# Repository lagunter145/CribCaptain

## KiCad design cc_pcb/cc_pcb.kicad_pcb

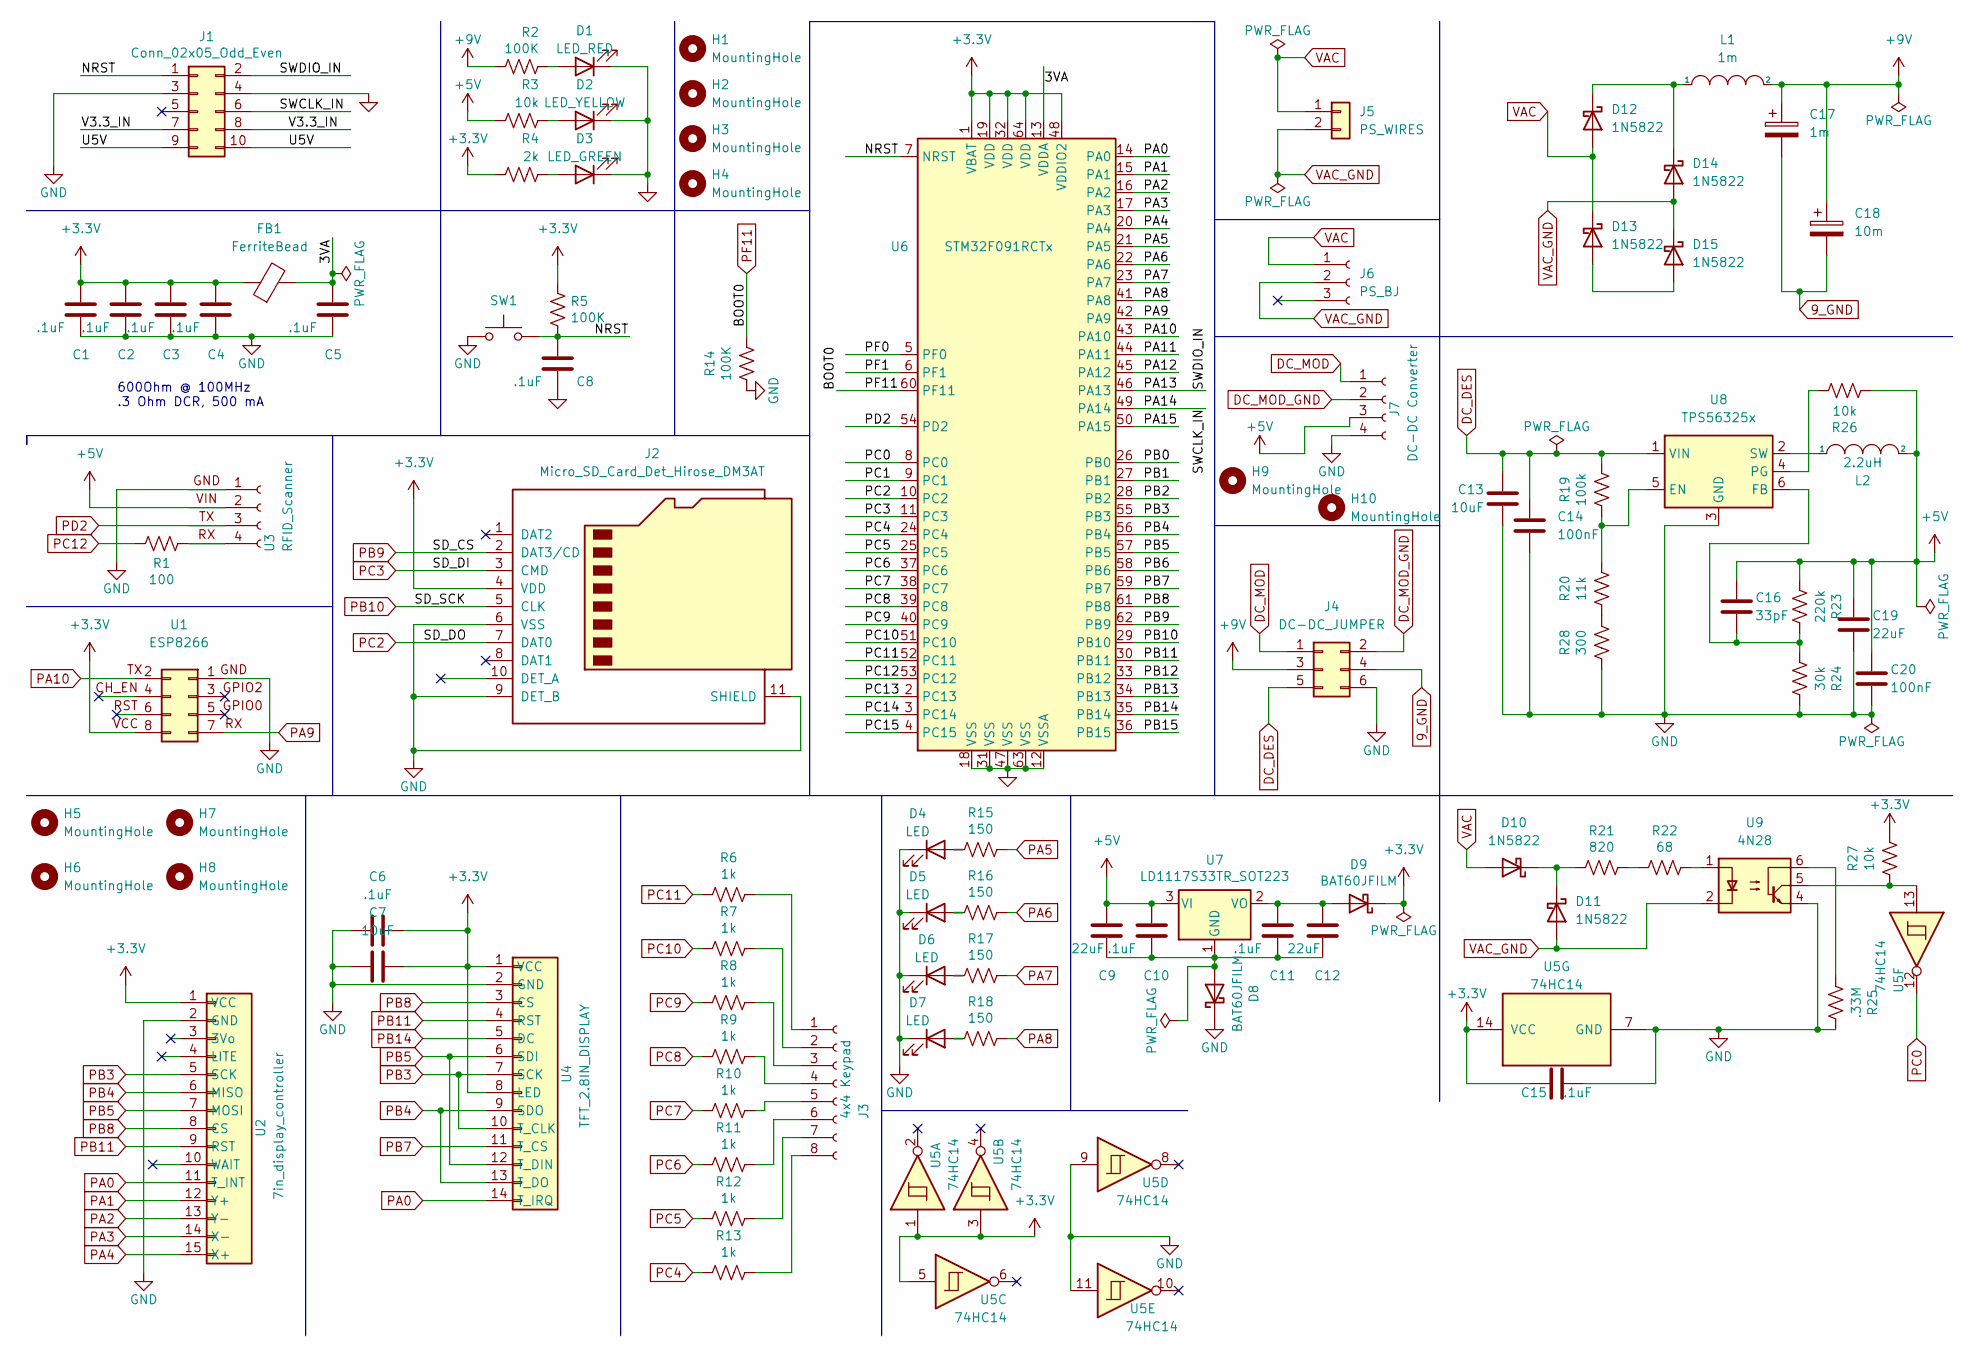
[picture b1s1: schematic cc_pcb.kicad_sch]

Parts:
C1, C2, C3, C4, C5, C6, C8, C10, C11, C15: .1uF; C_0805_2012Metric_Pad1.18x1.45mm_HandSolder
C7, C13: 10uF; C_0805_2012Metric_Pad1.18x1.45mm_HandSolder
C9, C12, C19: 22uF; C_0805_2012Metric_Pad1.18x1.45mm_HandSolder
C14, C20: 100nF; C_0805_2012Metric_Pad1.18x1.45mm_HandSolder
C16: 33pF; C_0805_2012Metric_Pad1.18x1.45mm_HandSolder
C17: 1m; CP_Radial_D12.5mm_P5.00mm
C18: 10m; C_Radial_D18.0mm_H35.5mm_P7.50mm
D1: LED_RED; LED_0805_2012Metric_Pad1.15x1.40mm_HandSolder
D2: LED_YELLOW; LED_0805_2012Metric_Pad1.15x1.40mm_HandSolder
D3: LED_GREEN; LED_0805_2012Metric_Pad1.15x1.40mm_HandSolder
D4, D5, D6, D7: LED; LED_D3.0mm
D8, D9: BAT60JFILM; D_SOD-323
D10, D11, D12, D13, D14, D15: 1N5822; DIO_1N5822
FB1: FerriteBead; R_0805_2012Metric_Pad1.20x1.40mm_HandSolder
H1, H2, H3, H4: MountingHole; MountingHole_8.4mm_M8
H5, H6, H7, H8, H9, H10: MountingHole; MountingHole_2.2mm_M2_ISO7380
J1: Conn_02x05_Odd_Even; IDC-Header_2x05_P2.54mm_Vertical
J2: Micro_SD_Card_Det_Hirose_DM3AT; microSD_HC_Hirose_DM3AT-SF-PEJM5
J3: 4x4 Keypad; 4x4_keypad
J4: DC-DC_JUMPER; PinSocket_2x03_P1.27mm_Vertical
J5: PS_WIRES; PS_2_Wire
J6: PS_BJ; barrel_jack_adapter
J7: DC-DC Converter; 7.5Vdc-5Vdc_buck_converter
L1: 1m; L_Toroid_Vertical_L54.0mm_W23.8mm_P20.10mm_Bourns_5700
L2: 2.2uH; L_0805_2012Metric_Pad1.15x1.40mm_HandSolder
R1: 100; R_0805_2012Metric_Pad1.20x1.40mm_HandSolder
R2, R5, R14: 100K; R_0805_2012Metric_Pad1.20x1.40mm_HandSolder
R3, R26, R27: 10k; R_0805_2012Metric_Pad1.20x1.40mm_HandSolder
R4: 2k; R_0805_2012Metric_Pad1.20x1.40mm_HandSolder
R6, R7, R8, R9, R10, R11, R12, R13: 1k; R_0805_2012Metric_Pad1.20x1.40mm_HandSolder
R15, R16, R17, R18: 150; R_0805_2012Metric_Pad1.20x1.40mm_HandSolder
R19: 100k; R_0805_2012Metric_Pad1.20x1.40mm_HandSolder
R20: 11k; R_0805_2012Metric_Pad1.20x1.40mm_HandSolder
R21: 820; R_0805_2012Metric_Pad1.20x1.40mm_HandSolder
R22: 68; R_0805_2012Metric_Pad1.20x1.40mm_HandSolder
R23: 220k; R_0805_2012Metric_Pad1.20x1.40mm_HandSolder
R24: 30k; R_0805_2012Metric_Pad1.20x1.40mm_HandSolder
R25: .33M; R_0805_2012Metric_Pad1.20x1.40mm_HandSolder
R28: 300; R_0805_2012Metric_Pad1.20x1.40mm_HandSolder
SW1: SW_Push; SW_SPST_PTS645
U1: ESP8266; XCVR_ESP8266-01_ESP-01
U2: 7in_display_controller; RA8875_TFT_Breakout
U3: RFID_Scanner; RFID_Reader_PCB
U4: TFT_2.8IN_DISPLAY; tft_2.8in_touch_display
U5: 74HC14; SN74HC14N
U6: STM32F091RCTx; LQFP-64_10x10mm_P0.5mm
U7: LD1117S33TR_SOT223; 5-3.3_buck_converter
U8: TPS56325x; SOT-563
U9: 4N28; DIP-6_W7.62mm

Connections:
9_GND: C17.2, C18.2, J4.4
+3V3: C1.1, C2.1, C3.1, C4.1, C6.2, C7.2, C15.1, D9.1 (K), FB1.1, J2.4 (VDD), R4.1, R5.1, R27.1, U1.8, U2.1 (VCC), U4.1 (VCC), U4.8 (LED), U5.1, U5.3, U5.5, U5.14 (VCC), U6.1 (VBAT), U6.19 (VDD), U6.32 (VDD), U6.48 (VDDIO2), U6.64 (VDD)
+5V: C9.1, C10.1, C16.1, C19.1, C20.1, J7.3, L2.2, R3.1, R23.2, R26.2, U3.2, U7.3 (VI)
+9V: C17.1, C18.1, J4.3, L1.2, R2.1
/3VA: C5.1, FB1.2, U6.13 (VDDA)
/NRST: C8.1, J1.1, R5.2, SW1.2, U6.7 (NRST)
/PA11: U6.44 (PA11)
/PA12: U6.45 (PA12)
/PA13: J1.2, U6.46 (PA13)
/PA14: J1.6, U6.49 (PA14)
/PA15: U6.50 (PA15)
/PB0: U6.26 (PB0)
/PB1: U6.27 (PB1)
/PB2: U6.28 (PB2)
/PB6: U6.58 (PB6)
/PB12: U6.33 (PB12)
/PB13: U6.34 (PB13)
/PB15: U6.36 (PB15)
/PC1: U6.9 (PC1)
/PC13: U6.2 (PC13)
/PC14: U6.3 (PC14)
/PC15: U6.4 (PC15)
/PF0: U6.5 (PF0)
/PF1: U6.6 (PF1)
/U5V: J1.9, J1.10
/V3.3_IN: J1.7, J1.8
DC_DES: C13.1, C14.1, J4.5, R19.1, U8.1 (VIN)
DC_MOD: J4.1, J7.1
DC_MOD_GND: J4.2, J7.2
GND: C1.2, C2.2, C3.2, C4.2, C5.2, C6.1, C7.1, C8.2, C13.2, C14.2, C15.2, C19.2, C20.2, D1.1 (K), D2.1 (K), D3.1 (K), D4.1 (K), D5.1 (K), D6.1 (K), D7.1 (K), D8.1 (K), J1.3, J1.4, J2.6 (VSS), J2.9 (DET_B), J2.11 (SHIELD), J4.6, J7.4, R14.2, R24.1, R25.1, R28.2, SW1.1, U1.1, U2.2 (GND), U3.1, U4.2 (GND), U5.7 (GND), U5.9, U5.11, U6.12 (VSSA), U6.18 (VSS), U6.31 (VSS), U6.47 (VSS), U6.63 (VSS), U8.3 (GND), U9.4
unnamed: C9.2, C10.2, C11.2, C12.2, D8.2 (A), U7.1 (GND)
unnamed: C11.1, C12.1, D9.2 (A), U7.2 (VO)
unnamed: C16.2, R23.1, R24.2, U8.6 (FB)
unnamed: D1.2 (A), R2.2
unnamed: D2.2 (A), R3.2
unnamed: D3.2 (A), R4.2
unnamed: D4.2 (A), R15.2
unnamed: D5.2 (A), R16.2
unnamed: D6.2 (A), R17.2
unnamed: D7.2 (A), R18.2
unnamed: D10.1 (K), D11.1 (K), R21.2
unnamed: D12.1 (K), D14.1 (K), L1.1
unnamed: D13.2 (A), D15.2 (A)
unnamed: J3.1, R6.1
unnamed: J3.2, R7.1
unnamed: J3.3, R8.1
unnamed: J3.4, R9.1
unnamed: J3.5, R10.1
unnamed: J3.6, R11.1
unnamed: J3.7, R12.1
unnamed: J3.8, R13.1
unnamed: L2.1, U8.2 (SW)
unnamed: R1.1, U3.4
unnamed: R19.2, R20.1, U8.5 (EN)
unnamed: R20.2, R28.1
unnamed: R21.1, R22.2
unnamed: R22.1, U9.1
unnamed: R25.2, U9.6
unnamed: R26.1, U8.4 (PG)
unnamed: R27.2, U5.13, U9.5
PA0: U2.11 (T_INT), U4.14 (T_IRQ), U6.14 (PA0)
PA1: U2.12 (Y+), U6.15 (PA1)
PA2: U2.13 (Y-), U6.16 (PA2)
PA3: U2.14 (X-), U6.17 (PA3)
PA4: U2.15 (X+), U6.20 (PA4)
PA5: R15.1, U6.21 (PA5)
PA6: R16.1, U6.22 (PA6)
PA7: R17.1, U6.23 (PA7)
PA8: R18.1, U6.41 (PA8)
PA9: U1.7, U6.42 (PA9)
PA10: U1.2, U6.43 (PA10)
PB3: U2.5 (SCK), U4.7 (SCK), U4.10 (T_CLK), U6.55 (PB3)
PB4: U2.6 (MISO), U4.9 (SDO), U4.13 (T_DO), U6.56 (PB4)
PB5: U2.7 (MOSI), U4.6 (SDI), U4.12 (T_DIN), U6.57 (PB5)
PB7: U4.11 (T_CS), U6.59 (PB7)
PB8: U2.8 (CS), U4.3 (CS), U6.61 (PB8)
PB9: J2.2 (DAT3/CD), U6.62 (PB9)
PB10: J2.5 (CLK), U6.29 (PB10)
PB11: U2.9 (RST), U4.4 (RST), U6.30 (PB11)
PB14: U4.5 (DC), U6.35 (PB14)
PC0: U5.12, U6.8 (PC0)
PC2: J2.7 (DAT0), U6.10 (PC2)
PC3: J2.3 (CMD), U6.11 (PC3)
PC4: R13.2, U6.24 (PC4)
PC5: R12.2, U6.25 (PC5)
PC6: R11.2, U6.37 (PC6)
PC7: R10.2, U6.38 (PC7)
PC8: R9.2, U6.39 (PC8)
PC9: R8.2, U6.40 (PC9)
PC10: R7.2, U6.51 (PC10)
PC11: R6.2, U6.52 (PC11)
PC12: R1.2, U6.53 (PC12)
PD2: U3.3, U6.54 (PD2)
PF11: R14.1, U6.60 (PF11)
VAC: D10.2 (A), D12.2 (A), D13.1 (K), J5.1, J6.1
VAC_GND: D11.2 (A), D14.2 (A), D15.1 (K), J5.2, J6.2, U9.2

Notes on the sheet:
600Ohm @ 100MHz .3 Ohm DCR, 500 mA

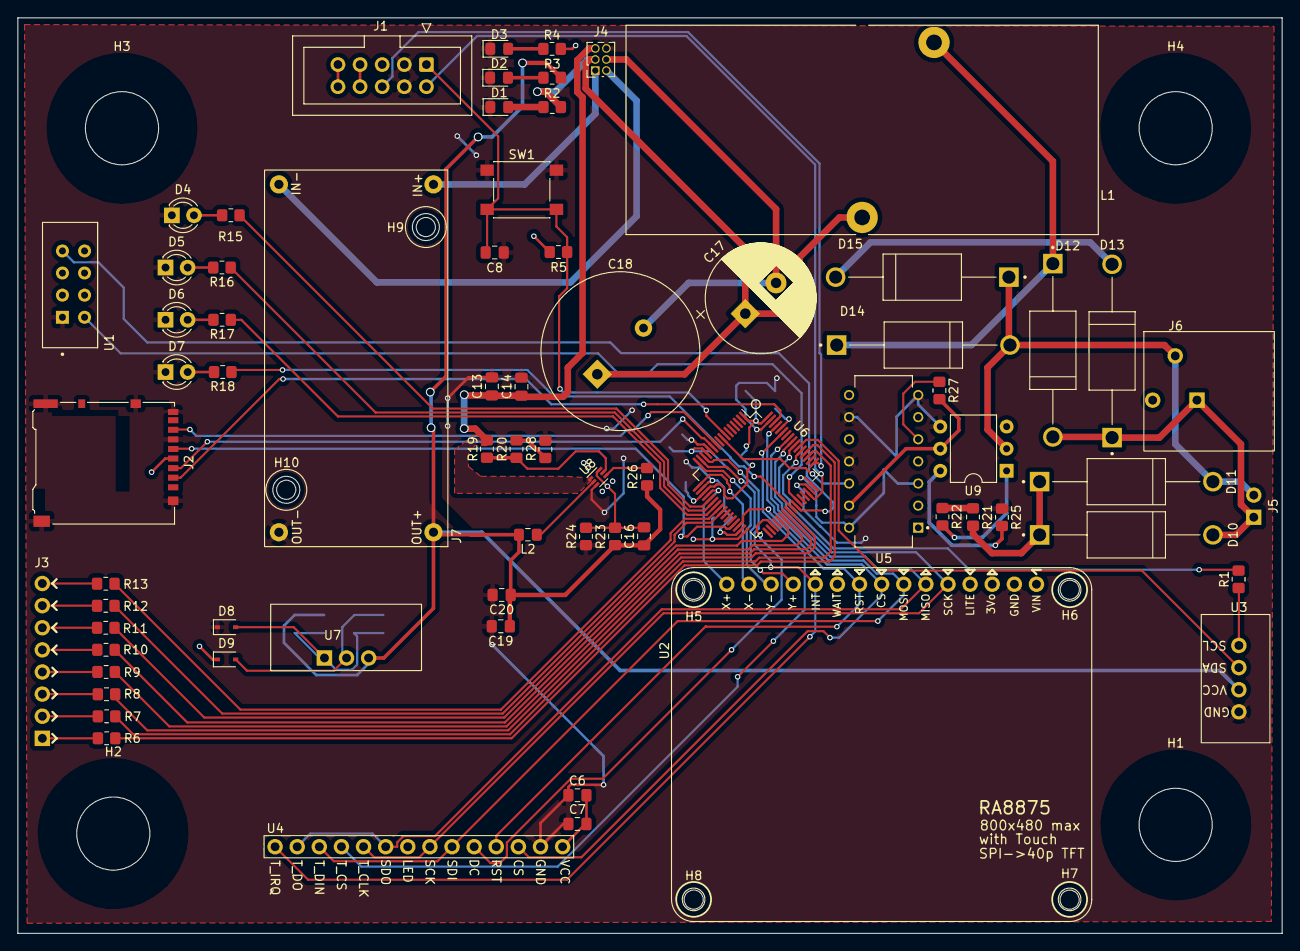
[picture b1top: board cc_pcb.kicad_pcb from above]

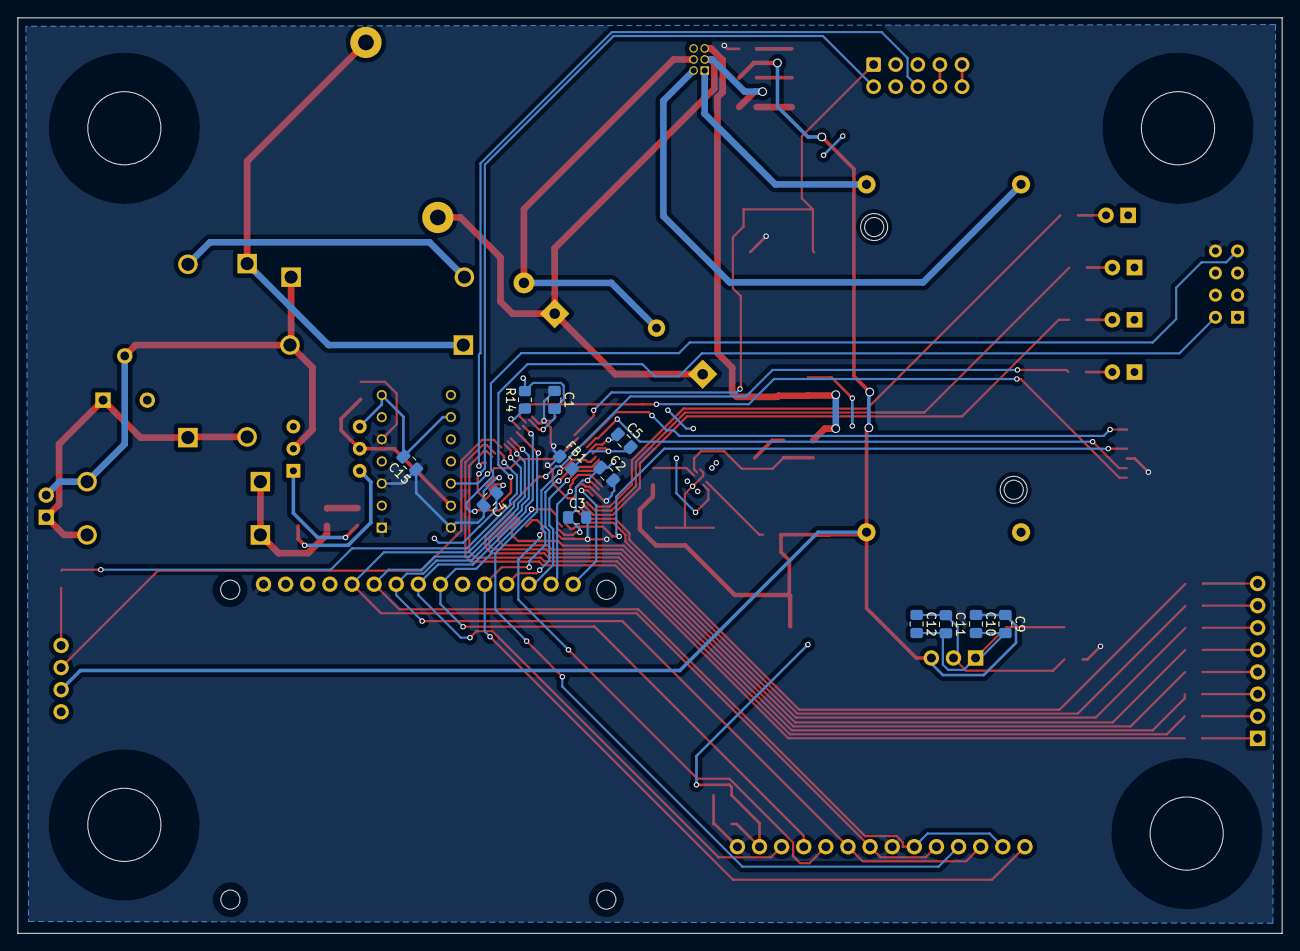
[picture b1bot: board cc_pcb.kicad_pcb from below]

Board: 2 copper layers, 145.2 x 105.1 mm, 93 parts (12 on the bottom side), 80 nets.

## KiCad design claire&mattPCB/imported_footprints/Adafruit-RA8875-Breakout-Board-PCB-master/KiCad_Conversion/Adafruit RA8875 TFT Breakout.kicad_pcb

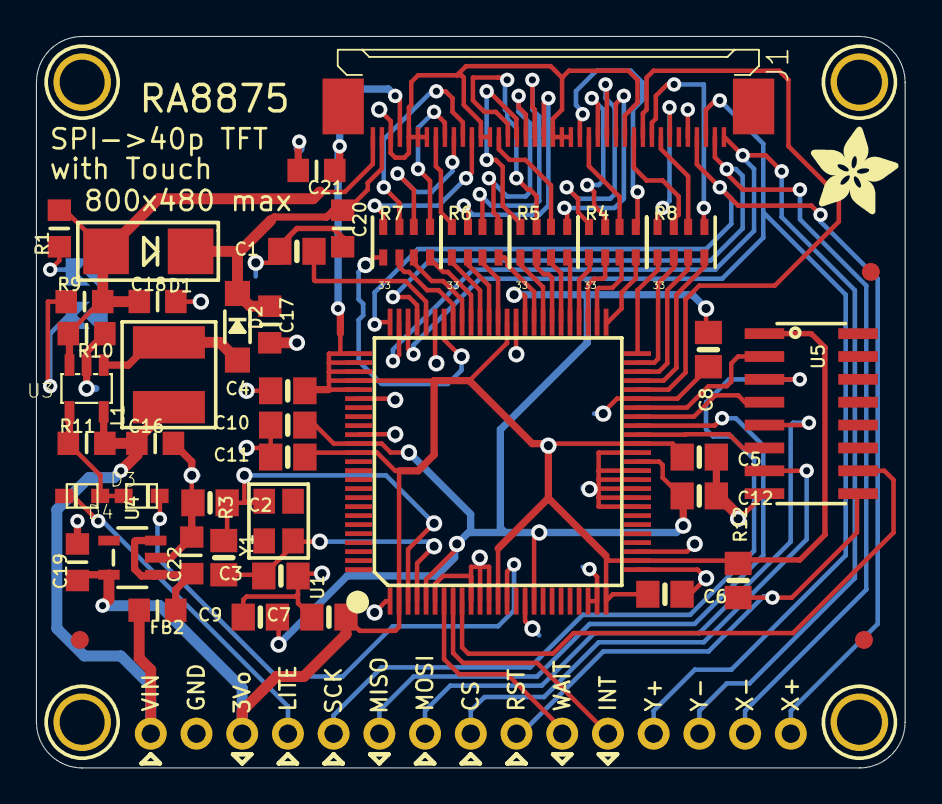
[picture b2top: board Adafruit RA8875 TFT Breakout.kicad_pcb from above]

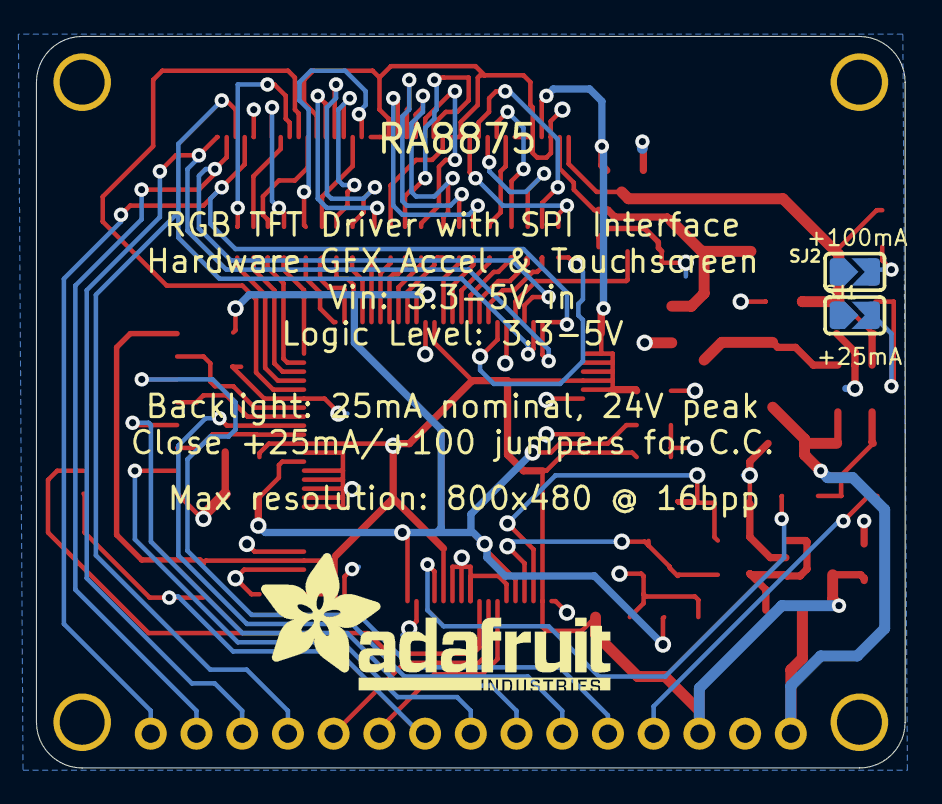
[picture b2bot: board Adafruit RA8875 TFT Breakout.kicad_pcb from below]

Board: 2 copper layers, 48.3 x 40.6 mm, 54 parts (3 on the bottom side), 72 nets.

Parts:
C1, C4, C5, C6, C7, C8, C9, C10, C11, C12: 0.1uF; 0805-NO
C2, C3: 20pF; 0805-NO
C16, C22: 10uF; _0805MP
C17, C20: 1uF; _0805MP
C18: 0.1uF; _0805MP
C19, C21: 10µF; _0805MP
D1: MM3Z24VT1G; SMADIODE
D2: MBR0540; SOD-123
D3, D4: 1N4148; SOD-323F
FB2: Ferrite; _0805MP
FID1, FID2, FID3: FIDUCIAL""; FIDUCIAL_1MM
J1: 40PINFPCM4-1734839-0; 4-1734839-0
JP1: Breakout; 1X15-CB
L1: 6.8uH large inductor; INDUCTOR_5X5MM_NR5040_NOTHERMALS
R1: 3Ω; _0805MP
R3: 1M; 0805-NO
R4, R5, R6, R7, R8: 33; RESPACK_4X0603
R9, R10: 12Ω; _0805MP
R11: 10K; _0805MP
R12: 10K; 0805-NO
SJ1: +25mA; SOLDERJUMPER_ARROW_NOPASTE
SJ2: +100mA; SOLDERJUMPER_ARROW_NOPASTE
U1: RA8875; LQFP100
U3: FAN5333BSX; SOT23-5@1
U4: MIC5225-3.3v; SOT23-5
U5: 74HC4050; SOIC16
U$18: ADAFRUIT_5MM
U$21, U$22, U$23, U$24: MOUNTINGHOLE2.5; MOUNTINGHOLE_2.5_PLATED
U$25: ADAFRUIT_TEXT_20MM
Y1: 20MHz; CRYSTAL_3.2X2.5

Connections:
1.5V: C8.1, C9.1, C10.1, C12.1, U1.5, U1.17, U1.38, U1.60, U1.86
+3V3: C4.1, C5.1, C6.1, C7.1, C11.1, C19.1, C21.1, J1.4, JP1.13, R12.2, U1.2, U1.13, U1.25, U1.27, U1.40, U1.62, U1.76, U1.77, U1.78, U1.79, U1.80, U1.87, U4.5, U5.1
+24V: C17.1, C20.1, D1.C, D2.C, J1.2
B3: J1.24, R4.5
B4: J1.25, R4.6
B5: J1.26, R4.7
B6: J1.27, R4.8
B7: J1.28, R5.5
BACKLITE: D4.C, JP1.12
CS: JP1.8, U5.7
DE: J1.34, R8.8
G2: J1.15, R5.6
G3: J1.16, R5.7
G4: J1.17, R5.8
G5: J1.18, R6.5
G6: J1.19, R6.6
G7: J1.20, R6.7
GND: C1.2, C2.1, C3.1, C4.2, C5.2, C6.2, C7.2, C8.2, C9.2, C10.2, C11.2, C12.2, C16.2, C17.2, C18.2, C19.2, C20.2, C21.2, C22.2, J1.3, J1.5, J1.6, J1.7, J1.13, J1.14, J1.21, J1.22, J1.23, J1.29, J1.36, JP1.14, R10.1, SJ1.1, SJ2.1, U1.1, U1.6, U1.10, U1.11, U1.12, U1.16, U1.23, U1.24, U1.26, U1.28, U1.33, U1.34, U1.35, U1.36, U1.37, U1.39, U1.45, U1.61, U1.70, U1.81, U1.85, U3.2, U4.2, U5.8
HSYNC: J1.32, R8.5
INT: JP1.5, U1.8
LEDK: C18.1, D1.A, J1.1, R1.2, R9.2, R10.2, U3.3
MISO: JP1.10, U1.42
MOSI: JP1.9, U5.5
MOSI_3V: U1.43, U5.4
unnamed: D2.A, L1.P$2, U3.1
unnamed: C2.2, R3.2, U1.3, Y1.2
unnamed: C1.1, U1.71
unnamed: R4.4, U1.51
unnamed: R4.3, U1.52
unnamed: R4.2, U1.53
unnamed: R4.1, U1.54
unnamed: R5.4, U1.55
unnamed: R5.3, U1.56
unnamed: R5.2, U1.57
unnamed: R5.1, U1.58
unnamed: R6.4, U1.59
unnamed: R6.3, U1.63
unnamed: R6.2, U1.64
unnamed: R6.1, U1.65
unnamed: R7.4, U1.66
unnamed: R7.3, U1.67
unnamed: R7.2, U1.68
unnamed: R7.1, U1.69
unnamed: R8.1, U1.50
unnamed: R8.2, U1.49
unnamed: R8.3, U1.48
unnamed: R8.4, U1.47
unnamed: R9.1, SJ1.2
unnamed: C22.1, FB2.1, U4.1, U4.3
unnamed: R1.1, SJ2.2
unnamed: C3.2, R3.1, U1.4, Y1.1
ON/OFF: J1.31, U1.46
PIXCLK: J1.30, R8.7
PWM0: D3.C, U1.14
R3: J1.8, R6.8
R4: J1.9, R7.5
R5: J1.10, R7.6
R6: J1.11, R7.7
R7: J1.12, R7.8
RESET: JP1.7, R12.1, U5.9
RESET_3V: U1.9, U5.10
SCK: JP1.11, U5.3
SHDN: D3.A, D4.A, R11.1, U3.4
SPI_CLK_3V: U1.44, U5.2
SPI_CS_3V: U1.41, U5.6
VIN: C16.1, FB2.2, JP1.15, L1.P$1, R11.2, U3.5
VSYNC: J1.33, R8.6
WAIT: JP1.6, U1.7
X+: J1.37, JP1.1, U1.75
X-: J1.39, JP1.2, U1.72
Y+: J1.38, JP1.4, U1.73
Y-: J1.40, JP1.3, U1.74

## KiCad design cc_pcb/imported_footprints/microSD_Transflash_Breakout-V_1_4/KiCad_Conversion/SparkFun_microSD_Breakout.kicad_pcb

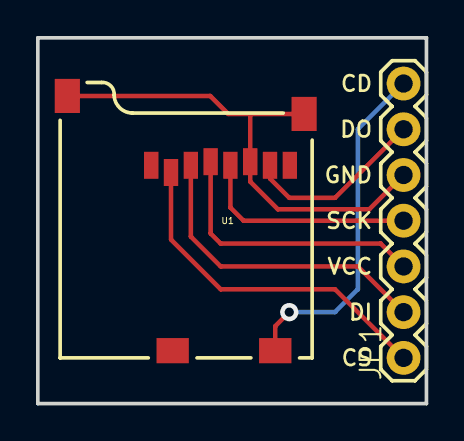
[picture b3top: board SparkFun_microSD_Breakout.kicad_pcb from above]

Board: 2 copper layers, 21.6 x 20.3 mm, 3 parts (1 on the bottom side), 7 nets.

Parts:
JP1: 1X07
U1: microSD; MICRO-SD-SOCKET-PP
U$1: LOGO-SFENEW; SFE-NEW-WEBLOGO

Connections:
CD1: JP1.7, U1.CD2
CS: JP1.1, U1.2
DI: JP1.2, U1.3
DO: JP1.6, U1.7
GND: JP1.5, U1.6, U1.GND1, U1.GND2
SCK: JP1.4, U1.5
VCC: JP1.3, U1.4

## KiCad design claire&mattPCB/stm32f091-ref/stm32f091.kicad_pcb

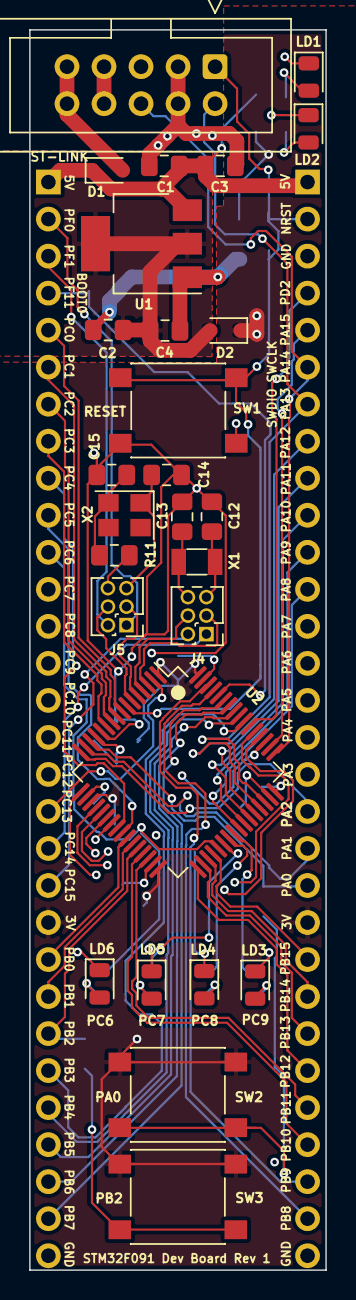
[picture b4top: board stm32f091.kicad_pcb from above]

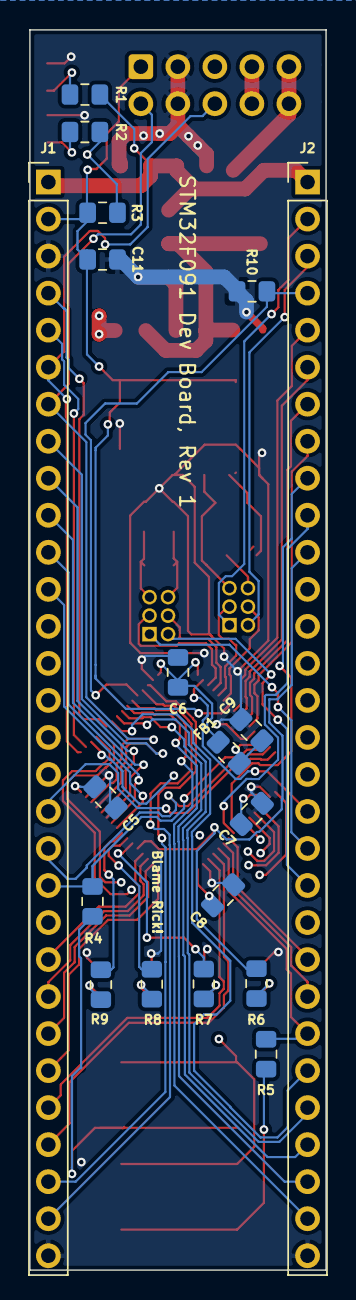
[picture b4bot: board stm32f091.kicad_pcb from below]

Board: 4 copper layers, 20.3 x 85.1 mm, 46 parts (19 on the bottom side), 77 nets.

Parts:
C1, C2: 22uF; C_0805_2012Metric_Pad1.15x1.40mm_HandSolder
C3, C4, C5, C6, C7, C8, C9, C11: .1uF; C_0805_2012Metric_Pad1.15x1.40mm_HandSolder
C12, C13: 12pF; C_0805_2012Metric_Pad1.15x1.40mm_HandSolder
C14, C15: 20pF; C_0805_2012Metric_Pad1.15x1.40mm_HandSolder
D1, D2: BAT60JFILM; D_SOD-323
FB1: Ferrite Bead; L_0805_2012Metric_Pad1.15x1.40mm_HandSolder
J1, J2: Conn_01x30_Male; HTSW-130-22-T-S
J3: Conn_02x05_Odd_Even; IDC-Header_2x05_P2.54mm_Vertical
J4, J5: Conn_02x03_Odd_Even; PinHeader_2x03_P1.27mm_Vertical
LD1, LD6: LED_Red; LED_0805_2012Metric
LD2, LD4: LED_Green; LED_0805_2012Metric
LD3: LED_Blue; LED_0805_2012Metric
LD5: LED_Yellow; LED_0805_2012Metric
R1: 5.1k; R_0805_2012Metric_Pad1.15x1.40mm_HandSolder
R2, R4, R5, R8: 1k; R_0805_2012Metric_Pad1.15x1.40mm_HandSolder
R3, R10: 100K; R_0805_2012Metric_Pad1.15x1.40mm_HandSolder
R6: 3k; R_0805_2012Metric_Pad1.15x1.40mm_HandSolder
R7: 2k; R_0805_2012Metric_Pad1.15x1.40mm_HandSolder
R9: 510; R_0805_2012Metric_Pad1.15x1.40mm_HandSolder
R11: 390; R_0805_2012Metric_Pad1.15x1.40mm_HandSolder
SW1, SW2, SW3: SW_Push; SW_SPST_PTS645
U1: LD1117S33TR_SOT223; SOT-223-3_TabPin2
U2: STM32F091RCTx; LQFP-64_10x10mm_P0.5mm
X1: 32.768kHz(12.5pF); ECX-.327-CDX-1293
X2: 8MHz(20pF); Crystal_SMD_3225-4Pin_3.2x2.5mm

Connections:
+3V0: C5.1, C6.1, C7.1, C8.1, D2.1, FB1.2, J1.21, J2.21, R2.1, R3.1, SW2.1, SW3.1, U2.1, U2.19, U2.32, U2.48, U2.64
+5V: C1.1, C3.1, D1.1, J1.1, J2.1, R1.1, U1.3
/3VA: C9.1, FB1.1, U2.13
/BOOT0: J2.4, R10.1, U2.60
/NRST: C11.1, J1.2, J3.1, R3.2, SW1.2, U2.7
/PA0: J1.20, R4.1, U2.14
/PA1: J1.19, U2.15
/PA2: J1.18, U2.16
/PA3: J1.17, U2.17
/PA4: J1.16, U2.20
/PA5: J1.15, U2.21
/PA6: J1.14, U2.22
/PA7: J1.13, U2.23
/PA8: J1.12, U2.41
/PA9: J1.11, U2.42
/PA10: J1.10, U2.43
/PA11: J1.9, U2.44
/PA12: J1.8, U2.45
/PA13: J1.7, J3.2, U2.46
/PA14: J1.6, J3.6, U2.49
/PA15: J1.5, U2.50
/PB0: J2.22, U2.26
/PB1: J2.23, U2.27
/PB2: J2.24, R5.1, U2.28
/PB3: J2.25, U2.55
/PB4: J2.26, U2.56
/PB5: J2.27, U2.57
/PB6: J2.28, U2.58
/PB7: J2.29, U2.59
/PB8: J1.29, U2.61
/PB9: J1.28, U2.62
/PB10: J1.27, U2.29
/PB11: J1.26, U2.30
/PB12: J1.25, U2.33
/PB13: J1.24, U2.34
/PB14: J1.23, U2.35
/PB15: J1.22, U2.36
/PC0: J2.5, U2.8
/PC1: J2.6, U2.9
/PC2: J2.7, U2.10
/PC3: J2.8, U2.11
/PC4: J2.9, U2.24
/PC5: J2.10, U2.25
/PC6: J2.11, R6.2, U2.37
/PC7: J2.12, R7.2, U2.38
/PC8: J2.13, R8.2, U2.39
/PC9: J2.14, R9.2, U2.40
/PC10: J2.15, U2.51
/PC11: J2.16, U2.52
/PC12: J2.17, U2.53
/PC13: J2.18, U2.2
/PC14: J4.3, U2.3
/PC15: J4.4, U2.4
/PD2: J1.4, U2.54
/PF0: J5.3, U2.5
/PF1: J5.4, U2.6
/U5V: D1.2, J3.9, J3.10
/V3.3_IN: J3.7, J3.8
/XPC14: J2.19, J4.1
/XPC15: J2.20, J4.2
/XPF0: J2.2, J5.1
/XPF1: J2.3, J5.2
GND: C1.2, C2.2, C3.2, C4.2, C5.2, C6.2, C7.2, C8.2, C9.2, C11.2, C12.2, C13.2, C14.2, C15.2, J1.3, J1.30, J2.30, J3.3, J3.4, LD1.1, LD2.1, LD3.1, LD4.1, LD5.1, LD6.1, R10.2, SW1.1, U1.1, U2.12, U2.18, U2.31, U2.47, U2.63
unnamed: C2.1, C4.1, D2.2, U1.2
unnamed: C12.1, J4.5, X1.1
unnamed: C13.1, J4.6, X1.2
unnamed: C14.1, J5.5, X2.1
unnamed: C15.1, R11.2, X2.2
unnamed: J5.6, R11.1
unnamed: LD1.2, R1.2
unnamed: LD2.2, R2.2
unnamed: LD3.2, R9.1
unnamed: LD4.2, R8.1
unnamed: LD5.2, R7.1
unnamed: LD6.2, R6.1
unnamed: R4.2, SW2.2
unnamed: R5.2, SW3.2

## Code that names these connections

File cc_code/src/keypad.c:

/*
 * keypad_test.c
 *
 *  Created on: Apr 14, 2023
 *      Author: gunter3
 */

#include <stdint.h>
#include "stm32f0xx.h"
#include "colors.h"
#include "keypad.h"

//extern volatile uint16_t base_color;
//extern volatile uint16_t acce_color;
//extern volatile uint16_t color_pairs[16][2];
//extern volatile uint8_t colorUpdated;

//enables GPIO ports for Keypad and LEDs
void enable_ports_keypad_LED(){
    //Keypad
    //turn on clock for keypad
    RCC->AHBENR |= RCC_AHBENR_GPIOCEN;
    //clear PC4-PC11 for Keypad
    GPIOC->MODER &= ~(GPIO_MODER_MODER4 |
                    GPIO_MODER_MODER5 |
                    GPIO_MODER_MODER6 |
                    GPIO_MODER_MODER7 |
                    GPIO_MODER_MODER8 |
                    GPIO_MODER_MODER9 |
                    GPIO_MODER_MODER10 |
                    GPIO_MODER_MODER11);

    //PC4-PC7: rows are inputs
    //PC4-PC7 pulled internally low
     GPIOC->PUPDR &= ~(GPIO_PUPDR_PUPDR4 |
                     GPIO_PUPDR_PUPDR5 |
                     GPIO_PUPDR_PUPDR6 |
                     GPIO_PUPDR_PUPDR7);
     GPIOC->PUPDR |= GPIO_PUPDR_PUPDR4_1 |
                     GPIO_PUPDR_PUPDR5_1 |
                     GPIO_PUPDR_PUPDR6_1 |
                     GPIO_PUPDR_PUPDR7_1;
     //PC8-PC11: columns are outputs
     GPIOC->MODER |= GPIO_MODER_MODER8_0 |
                 GPIO_MODER_MODER9_0 |
                 GPIO_MODER_MODER10_0 |
                 GPIO_MODER_MODER11_0;

     //LED
     //turn on clock for LEDs
      RCC->AHBENR |= RCC_AHBENR_GPIOAEN;
      //clear PC0-PC3 for LEDs
      GPIOA->MODER &= ~(GPIO_MODER_MODER5 |
                      GPIO_MODER_MODER6 |
                      GPIO_MODER_MODER7 |
                      GPIO_MODER_MODER8);
      //set PC0-PC3 for outputs
      GPIOA->MODER |= GPIO_MODER_MODER5_0 |
                      GPIO_MODER_MODER6_0 |
                      GPIO_MODER_MODER7_0 |
                      GPIO_MODER_MODER8_0;
}

//set up Timer 7 for Keypad
void setup_tim7() {
    RCC->APB1ENR|= RCC_APB1ENR_TIM7EN; //turn on clock

    //set timer to update event exactly once per millisecond (f = 1 kHz)
    TIM7->PSC = 4800 - 1;
    TIM7->ARR = 2500 - 1;

    //Update Interrupt enable
    TIM7->DIER |= TIM_DIER_UIE;
    //enable interrupt in NVIC ISER
    NVIC->ISER[0] |= (1 << TIM7_IRQn);
	NVIC_SetPriority(TIM7_IRQn, 3);
    //enable the counter
    TIM7->CR1 |= TIM_CR1_CEN;
}

//Timer 7 Handler for Keypad
void TIM7_IRQHandler()
{
    //acknowledge the interrupt
    TIM7->SR &= ~TIM_SR_UIF;

    for (int col = 1; col <= 4; col++){
        //clear all columns and set 'col' column to 1
        drive_column(col);

        //used to slow down the checking of the pins
        mysleep();

        //Given 'col' column is asserted, what rows are also asserted
        int row_val = read_rows();
        int row4 = (row_val >> 4) & 0x1;
        int row3 = (row_val >> 5) & 0x1;
        int row2 = (row_val >> 6) & 0x1;
        int row1 = (row_val >> 7) & 0x1;

        //key to convert asserted row and column to HEX value and update the color pairs
        //If a key is detected colorUpdated will become anything other than a 0
        //this will then be recognized in guiStateHandler during the once per second
        //interrupt from the timing synchronization
        colorUpdated |=  Keypad_to_LEDs(col, row1, row2, row3, row4);
    }
}

//Read the rows values of the keypad
int read_rows() {
    //isolate rows (PC4-PC7)
    int row_vals = (GPIOC->IDR & 0xF0);
    return row_vals;
}

//Drive one column of the keypad at a time
void drive_column(int col_val) {
    //clears columns
    GPIOC->ODR &= ~ (GPIO_ODR_8 |
                     GPIO_ODR_9 |
                     GPIO_ODR_10 |
                     GPIO_ODR_11);

    //sets col_val column to be 1
    GPIOC->ODR |= (0x1 << (7 + col_val));
}

//This function sets a GPIO pin num to val
void setn(int32_t pin_num, int32_t val) {
    if(val != 0)
    {
        //if value is not zero, set GPIO pin num to 1
        GPIOA->BSRR |= (0x1 << pin_num);
    }
    else
    {
        //if value is zero, set GPIO pin num to 0
        GPIOA->BSRR |= (0x1 << (pin_num + 16));
    }
}

//This functions uses the column and row that is asserted on the keyboard
//to light the LEDs (showing the HEX equivalent of the button pressed)
int Keypad_to_LEDs(int col_val, int row1, int row2, int row3, int row4){
    //Display HEX value of keyboard input on LEDs

    uint8_t val = 0;
    if(col_val == 4){
        if(row1 == 1){
            //HEX: 1
            base_color = color_pairs[0][0];
        	acce_color = color_pairs[0][1];
            val = '1';
        }
        else if(row2 == 1){
            //HEX: 4
        	base_color = color_pairs[3][0];
        	acce_color = color_pairs[3][1];
            val = '4';

        }
        else if(row3 == 1){
            //HEX: 7
        	base_color = color_pairs[6][0];
        	acce_color = color_pairs[6][1];
            val = '7';
        }
        else if(row4 == 1)  {
            //HEX: * -- treated as E for the purpose of this test
        	base_color = color_pairs[13][0];
        	acce_color = color_pairs[13][1];
            val = '*';
        }
    }
    else if(col_val == 3){
        if(row1 == 1){
            //HEX:2
        	base_color = color_pairs[1][0];
        	acce_color = color_pairs[1][1];
            val = '2';
        }
        else if(row2 == 1){
            //HEX: 5
        	base_color = color_pairs[4][0];
        	acce_color = color_pairs[4][1];
            val = '5';
        }
        else if(row3 == 1){
            //HEX: 8
        	base_color = color_pairs[7][0];
        	acce_color = color_pairs[7][1];
            val = '8';
        }
        else if(row4 == 1){
            //HEX: 0
        	uint16_t temp = base_color;
        	base_color = acce_color;
        	acce_color = temp;
            val = '0';
        }
    }
    else if(col_val == 2){
        if(row1 == 1){
            //HEX: 3
        	base_color = color_pairs[2][0];
        	acce_color = color_pairs[2][1];
            val = '3';
        }
        else if(row2 == 1){
            //HEX: 6
        	base_color = color_pairs[5][0];
        	acce_color = color_pairs[5][1];
            val = '6';
        }
        else if(row3 == 1){
            //HEX: 9
        	base_color = color_pairs[8][0];
        	acce_color = color_pairs[8][1];
            val = '9';
        }
        else if(row4 == 1) {
            //HEX: # -- treated as F for purpose of this test
        	uint16_t temp = base_color;
			base_color = acce_color;
        	acce_color = temp;
            val = '#';
        }
    }
    else if(col_val == 1){
        if(row1 == 1){
            //HEX: A
        	base_color = color_pairs[9][0];
        	acce_color = color_pairs[9][1];
            val = 'A';
        }
        else if(row2 == 1){
            //HEX: B
        	base_color = color_pairs[10][0];
        	acce_color = color_pairs[10][1];
            val = 'B';
        }
        else if(row3 == 1){
            //HEX: C
        	base_color = color_pairs[11][0];
        	acce_color = color_pairs[11][1];
            val = 'C';
        }
        else if(row4 == 1){
            //HEX: D
            val = 'D';
            base_color = color_pairs[12][0];
            acce_color = color_pairs[12][1];
        }
    }

    return val;
}

//This function slows down the scanning of the rows
//Without this, it will scan too fast
void mysleep(void) {
    for(int n = 0; n < 1000; n++);
}

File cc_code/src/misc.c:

/*
 * misc.c
 *
 *  Created on: Mar 9, 2023
 *      Author: mrahf
 *      includes miscellaneous functions
 */

#include "stm32f0xx.h"
#include "misc.h"

//sets up PC6-PC9 to be LEDs because of the 362 board
void setup_devboard_leds() {
	//Enable RCC clocks to GPIOC
	RCC->AHBENR |= RCC_AHBENR_GPIOCEN;
	//Configure PA9-PC9 as output
	GPIOC->MODER &= ~(GPIO_MODER_MODER6 | GPIO_MODER_MODER7 | GPIO_MODER_MODER8 | GPIO_MODER_MODER9);
	GPIOC->MODER |= GPIO_MODER_MODER6_0 | GPIO_MODER_MODER7_0 | GPIO_MODER_MODER8_0 | GPIO_MODER_MODER9_0;

}

//Sets PA5-PA8 as LEDS for the PCB boards LEDs
void setup_pcb_leds() {
	//Enable RCC clocks to GPIOC
	RCC->AHBENR |= RCC_AHBENR_GPIOAEN;
	//Configure PA5-PA8 as output
	GPIOA->MODER &= ~(GPIO_MODER_MODER5 | GPIO_MODER_MODER6 | GPIO_MODER_MODER7 | GPIO_MODER_MODER8);
	GPIOA->MODER |=   GPIO_MODER_MODER5_0 | GPIO_MODER_MODER6_0 | GPIO_MODER_MODER7_0 | GPIO_MODER_MODER8_0;


}

//sets a GPIO pin high or low. high if on is 1 or low if on is 0
void set_pin(GPIO_TypeDef * gpio, char pin, char on) {
	//shifts to get the right pin
	uint32_t pinValue = 1 << pin;
	//if pin is low, so shift to get to the Bit Reset part of the register
	if (!on)
		pinValue = pinValue << 16;

	//sets the specific pin high
	gpio->BSRR |= pinValue;
}

//toggles a GPIO pin
void toggle_pin(GPIO_TypeDef * gpio, char pin) {
	//shifts the pin to get the right pin
	uint32_t pinValue = 1 << pin;

	//if the pin is high, then set it low
	//if the pin is low, then set it high
	set_pin(gpio, pin, !(gpio->ODR & pinValue));
}

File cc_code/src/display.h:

/*
 * display.h
 *
 *  Created on: Jan 24, 2023
 *      Author: Lauren
 */

#ifndef DISPLAY_H_
#define DISPLAY_H_

#define SPI SPI1

void nano_wait(unsigned int);

// display's chip select: PB8
#define CS_NUM  8
#define CS_BIT  (1<<CS_NUM)
#define CS_HIGH do { GPIOB->BSRR = GPIO_BSRR_BS_8; } while(0)
#define CS_LOW do { GPIOB->BSRR = GPIO_BSRR_BR_8; } while(0)
// display's touch feature chip select: PB9
#define CST_NUM  9
#define CST_BIT  (1<<CST_NUM)
#define CST_HIGH do { GPIOB->BSRR = GPIO_BSRR_BS_9; } while(0)
#define CST_LOW do { GPIOB->BSRR = GPIO_BSRR_BR_9; } while(0)
// display's reset: PB11
#define RESET_NUM 11
#define RESET_BIT (1<<RESET_NUM)
#define RESET_HIGH do { GPIOB->BSRR = GPIO_BSRR_BS_11; } while(0)
#define RESET_LOW  do { GPIOB->BSRR = GPIO_BSRR_BR_11; } while(0)
// display's DC: PB14
#define DC_NUM 14
#define DC_BIT (1<<DC_NUM)
#define DC_HIGH do { GPIOB->BSRR = GPIO_BSRR_BS_14; } while(0)
#define DC_LOW  do { GPIOB->BSRR = GPIO_BSRR_BR_14; } while(0)
// display's SCK
#define SCK_NUM 3
#define SCK_BIT (1<<SCK_NUM)
#define SCK_HIGH do { GPIOB->BSRR = GPIO_BSRR_BS_3; } while(0)
#define SCK_LOW  do { GPIOB->BSRR = GPIO_BSRR_BR_3; } while(0)
// display's SCK
#define CLK_NUM 3
#define CLK_BIT (1<<SCK_NUM)
#define CLK_HIGH do { GPIOB->BSRR = GPIO_BSRR_BS_3; } while(0)
#define CLK_LOW  do { GPIOB->BSRR = GPIO_BSRR_BR_3; } while(0)
// touch's DIN
#define DIN_NUM 5
#define DIN_BIT (1<<DIN_NUM)
#define DIN_HIGH do { GPIOB->BSRR = GPIO_BSRR_BS_5; } while(0)
#define DIN_LOW  do { GPIOB->BSRR = GPIO_BSRR_BR_5; } while(0)
// touch's DIN
#define DIN_NUM 5
#define DIN_BIT (1<<DIN_NUM)
#define DIN_HIGH do { GPIOB->BSRR = GPIO_BSRR_BS_5; } while(0)
#define DIN_LOW  do { GPIOB->BSRR = GPIO_BSRR_BR_5; } while(0)


#endif /* DISPLAY_H_ */

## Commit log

2023-01-18 started pcb kicad project and added stm32 stuff to schematic
2023-01-18 started Eclipse project for code
2023-01-24 3.5 inch display without touch setup included in lcd.c
2023-01-25 t_irq added so that when user touches screen, it registers
2023-01-25 add to gitignore
2023-01-26 schematic for 2.8in touch display with all pins connected
2023-01-27 add language settings xml to gitignore
2023-01-27 Reading from SPI for display's touch
2023-01-30 create rfid files
2023-01-30 basic UART read/write functions, untested.
2023-01-31 copied over functions from Elechouse libraries
2023-02-01 schematics for keypad, lights, 7in display, separate SPI's for 2.8in
2023-02-01 trying different ways to implement touch display's comms on 1 SPI
2023-02-02 changed datatypes of functions
2023-02-03 added back waiting for RXNE bit to read
2023-02-05 SPI-40Pin controller touch added and keypad mod in pcb schematic
2023-02-06 ltspice simulation for sine to square wave converter
2023-02-06 LTSpice simulation for converting a sine to a square wave with same frequency
2023-02-06 wi-fi module, RFID scanner, sineToSquare converter, AC-DC converter
2023-02-06 footprints for IN5822 and RA8875
2023-02-06 removed github repo linking from RA8875 project
2023-02-06 SD Card Reader Schematic
2023-02-07 footprints for SD Card Reader
2023-02-07 4x4 keypad footprint
2023-02-07 linked 4x4 keypad footprint to schematic
2023-02-07 fixed receive() return type to uint
2023-02-08 rounded corner edge cuts and silkscreen for pin labels
2023-02-08 folder for hardware assembly, PN532 V3 RFID model
2023-02-08 2 separate SPI's for 2.8in TFT display and touch
2023-02-08 FillScreen algo adapted from Adafruit RA8775, not init
2023-02-08 minor changes
2023-02-09 initialize display
2023-02-09 ESP8266 footprint and ran electrical check
2023-02-09 organized schematic and separated power supply by modules and our design
2023-02-10 display not working, changed init, testing w arduino
2023-02-10 footprint for barrel jack adapter
2023-02-10 buck rectifier circuit (values wrong), changed how power flags were
2023-02-10 buck converter module cad
2023-02-11 voltage converter module footrints, all components have footprints, BOM
2023-02-11 generated netlist and fixed errors from PCB editing tool
2023-02-14 keypad 3D blueprint
2023-02-14 footprints for every component, pcb footprint layout
2023-02-14 v base casing blueprint
2023-02-14 TPS56325x schematic symbol and footprint
2023-02-15 RA8875 and ESP8266 updated footprints
2023-02-15 added 2.8in tft display in addition to 7in one
2023-02-17 Can read 1 RFID card passively
2023-02-21 micro sd connector schematic/footprint, lm324 footprint
2023-02-22 able to fill screen of display
2023-02-22 updated symbols to include pin names to get rid of ERC warnings
2023-02-22 PCB for 362 development board
2023-02-22 passed ERC and footprints assigned
2023-02-22 moved all 3D files of PCB into hardware assembly folder
2023-02-23 create byte transfer function
2023-02-24 SPI read function working
2023-02-24 initial PCB components, traces laid out with DRC passed
2023-02-24 1:1 footprint changes and layout modded to follow rules
2023-02-25 cleaned up code, touch polling works
2023-02-27 PCB version 2.0
2023-02-28 added text functions
2023-02-28 updated schematic with text descriptions for each block. Also, added 0 ohm resistor and 10 ohm current limiting resistor to pcb. Minor changes were made to the designed buck converter circuit.
2023-02-28 added fantabulous silkscreen names to the board (schmack dab in the middle)
2023-03-01 no DRC warnings
2023-03-08 added oscillator for micro
2023-03-08 added diodes pointing to where 5V outputs
2023-03-08 diodes and vias w labels added
2023-03-10 touch read moved to EXTI interrupt
2023-03-21 last commit before pulling - matthew
2023-03-21 pcb finalization
2023-03-22 wifi: added httprequest function and a semaphore system to timer 6. This will allow there to be delay between different AT commands. timesync: added a basic time system that can be displayed on the 7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
2023-03-24 color changing button!
2023-03-25 wifi: added a more refined http get request that has host header and can now interface with worldclockapi.com. Tried to parse information, but was struggling to read anything being recieved by PA10. 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
2023-03-25 wifi: resolved issue with wifi_getchar
2023-03-28 wifi: finished wifi-time demo (2/27/23) (Matthew and Philip)
2023-03-29 wifi: added second accuracy and fixed it counting to 60 seconds and 60 minutes (Matthew)
2023-03-29 rfid: began to write DMA access info (Matthew)
2023-03-29 wrote simple led main code to test pcb mirco (Matt)
2023-03-30 Add files via upload
    Keypad Stuff
2023-03-31 rfid: using a different module, the new dma code began to work. It works now with one card. The address for th CSELR register was fixed from 0x400202A0 to 0x400200A8 (Matthew and Philip)
2023-04-05 updated to properly read uid's into global array
    disable DMA after receiving a uid packet and writing another command to passive scan for another card. reenable after to prevent the command's ACK frame response from filling the uid buffer.
2023-04-05 working demo for checking off PCB Touch, wifi, timing synch, and display for PSSCS. ManLab 4/5/2023 (Matt)
2023-04-07 wifi: added rudimentary error handling (Matthew)
2023-04-10 removed some artifacts of original library code
2023-04-10 realigned uid extraction in DMA handler
    the DMA buffer will fill with the response preamble, length, checksum, etc.
2023-04-11 removing files from gitignre
2023-04-11 remove .project from gitignore
2023-04-12 added untracked pcb files
2023-04-12 move rfid main into separate file
    so that when merged we don't lose the startup sequence
2023-04-12 added rfid init back to main
2023-04-12 rfid: got demo working for manlab show me a thing. wifi: added error handling for when the wifi disconnects (Philip & Matthew)
2023-04-13 time sync: added deboucing to the PC13 interrupt. hopefully it works. needs to test overnight to see what the error is (Matt)
2023-04-13 gui: added basic menu state machines (Matthew)
2023-04-14 broken code trying to implement states (matt)
2023-04-15 keypad: changed to un-debounced version. made it manipulate colors for GUI. wifi: fixed priorities to get wifi to work again (P-man & M-dawg)
2023-04-15 rfid: integrated rfid fully. gui: added basic checkin menu state (Philip)
2023-04-16 gui: added buttons to increment, decrement, enter the rfid guest check-in. Also refactored a lot of the GUI code to clean that bad boy up. Still lots to clean (mdog)
2023-04-16 check in screen doesn't fully redraw, time can now be toggled to show seconds
2023-04-16 centered text for buttons
2023-04-17 check in and roommate working
2023-04-17 wifi: added wifi connected and time acquired state variables. Also moved the menu draw out of the wifi usart irq to avoid spi interruptions (matty)
2023-04-18 cleaned up comments. moved around global variable declarations so all externs are in header files. (philip)
2023-04-19 ece 362 sd card lab
2023-04-19 more sd card include files
2023-04-19 the header files for the sd card
2023-04-20 can communicate with web server to pull each roommate's data including whether they're checked in, how many guests they have, and their events. updates local structs with this data to display on GUI.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
2023-04-21 chore scheduling, refresh
2023-04-21 wifi: added refresh functions for the wifi to communicate with the server and update the device's local values. gui: added refresh menu and chores (Matt & lauren)
2023-04-21 add display -> server change on chores
2023-04-26 state of the project as of final demo
2023-04-27 final working version with hopefully no more locking up (philip)
